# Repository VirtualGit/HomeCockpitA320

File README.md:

# A320 Home Cockpit
Home cockpit project of the Airbus A320 based on Arduino.

[Read more](https://github.com/VirtualGit/HomeCockpitA320/wiki/A320-Home-Cockpit)

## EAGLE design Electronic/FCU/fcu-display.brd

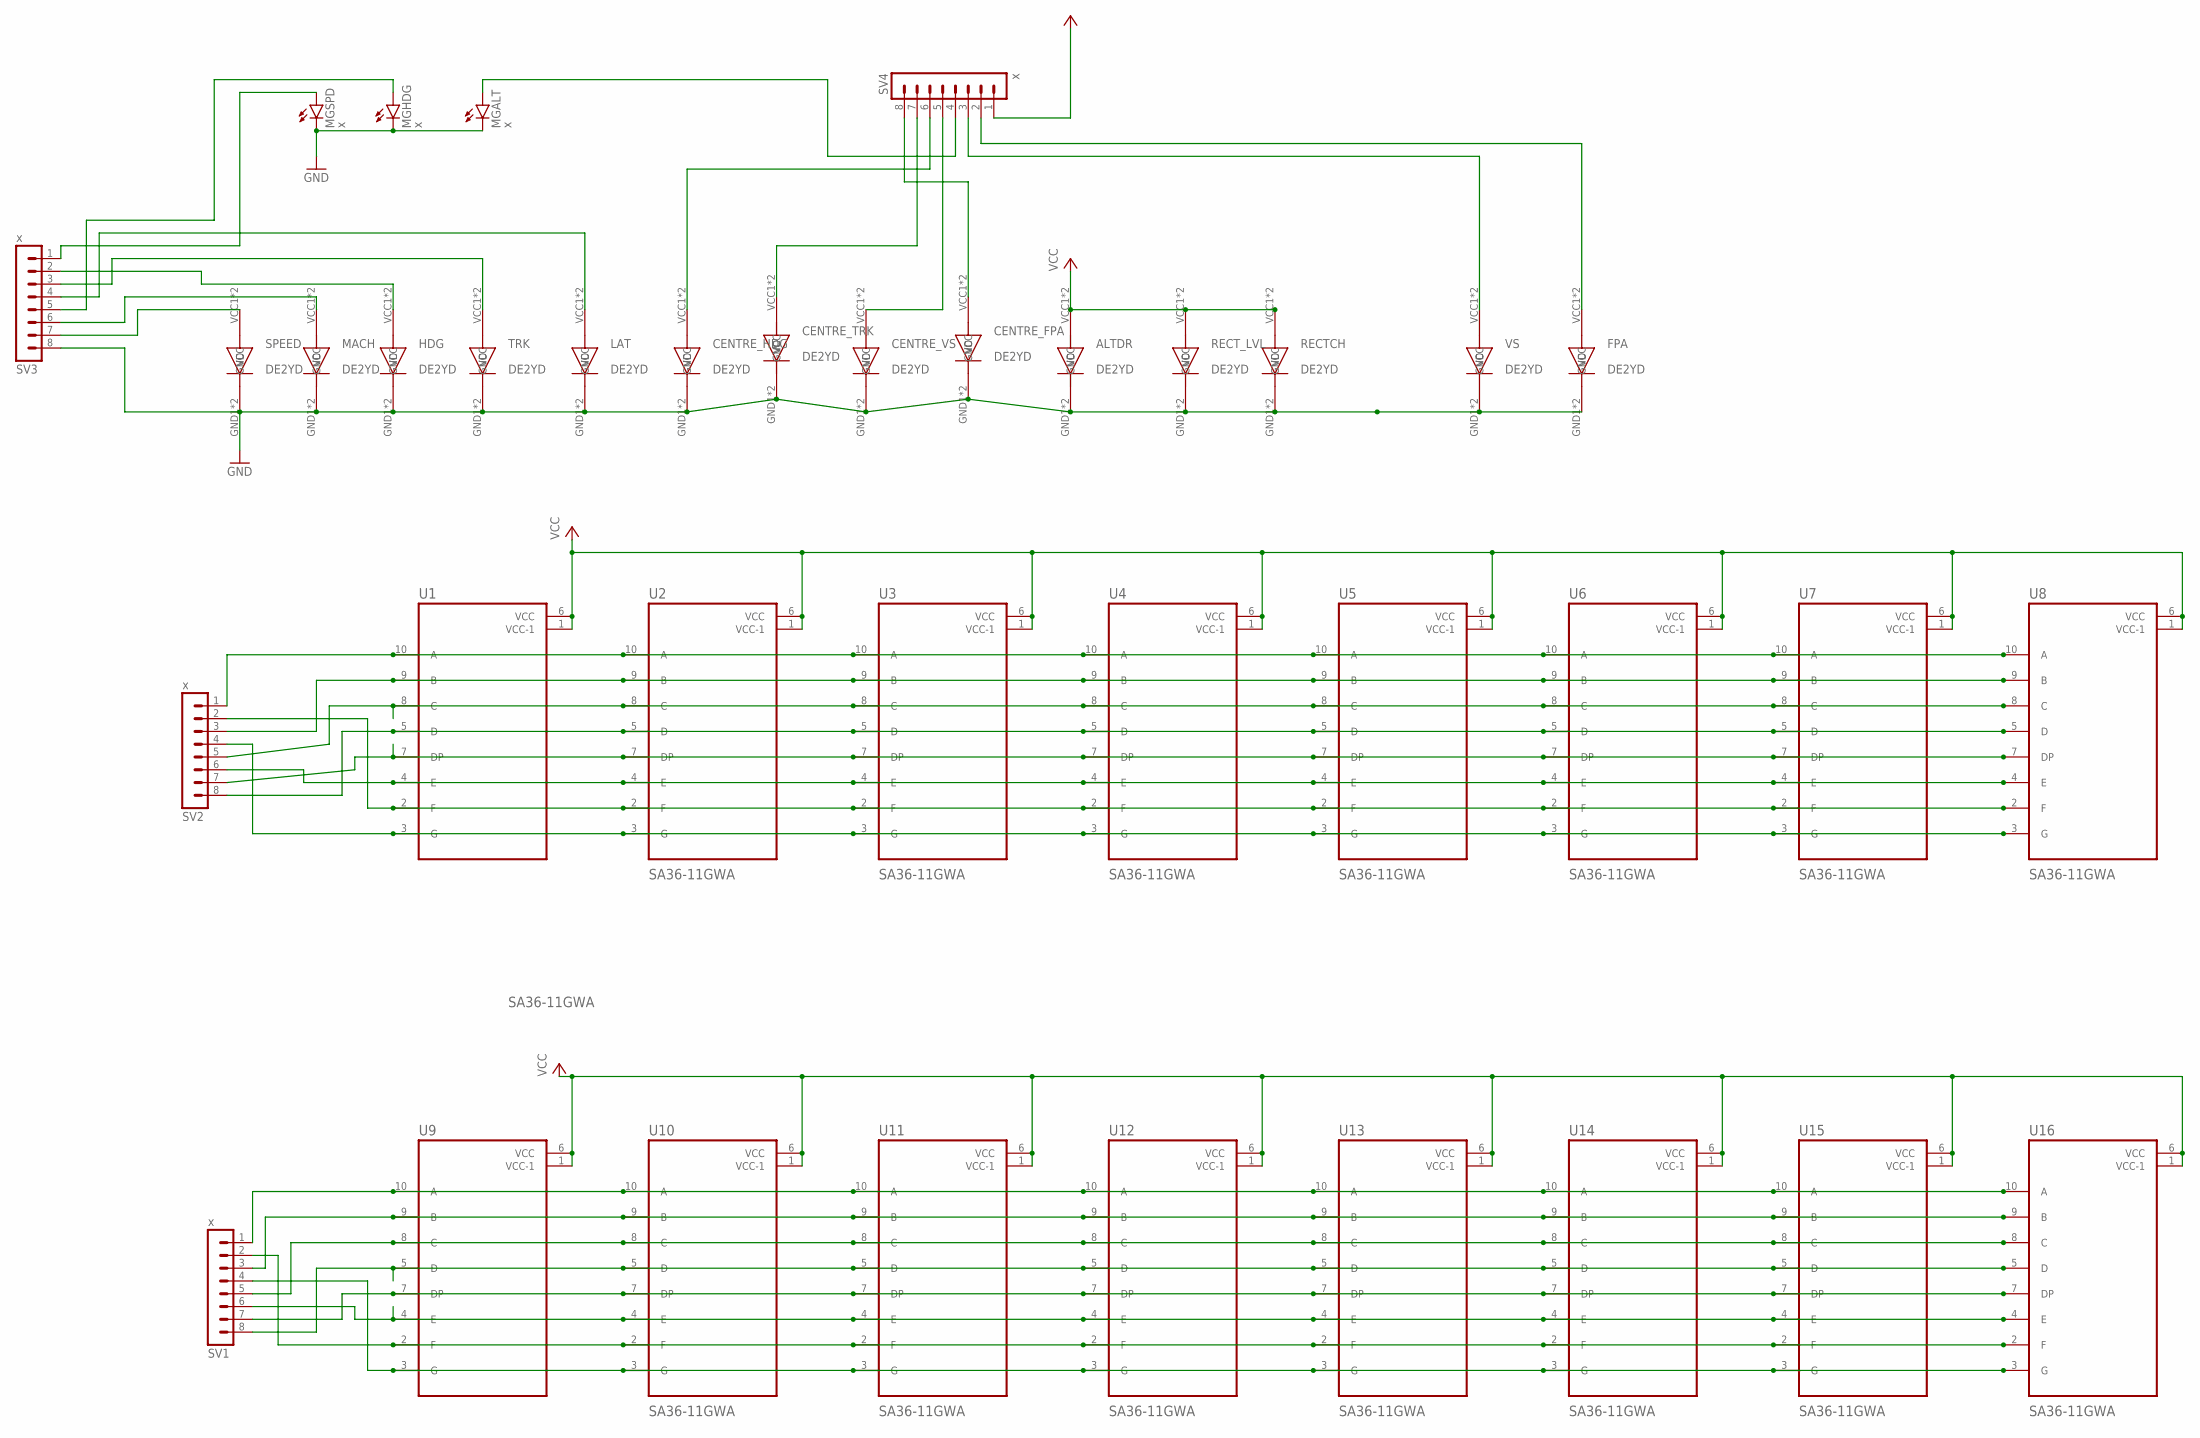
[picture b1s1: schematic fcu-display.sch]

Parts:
ALTDR: DE2YD; STANDARD
CENTRE_FPA: DE2YD; STANDARD
CENTRE_HDG: DE2YD; STANDARD
CENTRE_TRK: DE2YD; STANDARD
CENTRE_VS: DE2YD; STANDARD
FPA: DE2YD; STANDARD
HDG: DE2YD; STANDARD
LAT: DE2YD; STANDARD
MACH: DE2YD; STANDARD
MGALT: x; LED3MM
MGHDG: x; LED3MM
MGSPD: x; LED3MM
RECTCH: DE2YD; STANDARD
RECT_LVL: DE2YD; STANDARD
SPEED: DE2YD; STANDARD
SV1, SV2, SV3, SV4: x; MA08-1
TRK: DE2YD; STANDARD
U1, U2, U3, U4, U5, U6, U7, U8, U9, U10, U11, U12, U13, U14, U15, U16: SA36-11GWA; KINGBRIGHT_SC36-11SRWA
VS: DE2YD; STANDARD

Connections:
GND: ALTDR.GND1 (GND), ALTDR.GND2 (GND), CENTRE_FPA.GND1 (GND), CENTRE_FPA.GND2 (GND), CENTRE_HDG.GND1 (GND), CENTRE_HDG.GND2 (GND), CENTRE_TRK.GND1 (GND), CENTRE_TRK.GND2 (GND), CENTRE_VS.GND1 (GND), CENTRE_VS.GND2 (GND), FPA.GND1 (GND), FPA.GND2 (GND), HDG.GND1 (GND), HDG.GND2 (GND), LAT.GND1 (GND), LAT.GND2 (GND), MACH.GND1 (GND), MACH.GND2 (GND), MGALT.K (C), MGHDG.K (C), MGSPD.K (C), RECTCH.GND1 (GND), RECTCH.GND2 (GND), RECT_LVL.GND1 (GND), RECT_LVL.GND2 (GND), SPEED.GND1 (GND), SPEED.GND2 (GND), SV3.8, TRK.GND1 (GND), TRK.GND2 (GND), VS.GND1 (GND), VS.GND2 (GND)
unnamed: SV2.1, U1.10 (A), U2.10 (A), U3.10 (A), U4.10 (A), U5.10 (A), U6.10 (A), U7.10 (A), U8.10 (A)
unnamed: LAT.VCC1 (VCC), LAT.VCC2 (VCC), SV3.4
unnamed: SV2.5, U1.8 (C), U2.8 (C), U3.8 (C), U4.8 (C), U5.8 (C), U6.8 (C), U7.8 (C), U8.8 (C)
unnamed: MGSPD.A, SV3.1
unnamed: SV2.7, U1.7 (DP), U2.7 (DP), U3.7 (DP), U4.7 (DP), U5.7 (DP), U6.7 (DP), U7.7 (DP), U8.7 (DP)
unnamed: MGHDG.A, SV3.5
unnamed: SV2.2, U1.2 (F), U2.2 (F), U3.2 (F), U4.2 (F), U5.2 (F), U6.2 (F), U7.2 (F), U8.2 (F)
unnamed: FPA.VCC1 (VCC), FPA.VCC2 (VCC), SV4.2
unnamed: SV4.3, VS.VCC1 (VCC), VS.VCC2 (VCC)
unnamed: CENTRE_FPA.VCC1 (VCC), CENTRE_FPA.VCC2 (VCC), SV4.8
unnamed: CENTRE_TRK.VCC1 (VCC), CENTRE_TRK.VCC2 (VCC), SV4.7
unnamed: CENTRE_HDG.VCC1 (VCC), CENTRE_HDG.VCC2 (VCC), SV4.6
unnamed: SV1.1, U9.10 (A), U10.10 (A), U11.10 (A), U12.10 (A), U13.10 (A), U14.10 (A), U15.10 (A), U16.10 (A)
unnamed: SPEED.VCC1 (VCC), SPEED.VCC2 (VCC), SV3.7
unnamed: MACH.VCC1 (VCC), MACH.VCC2 (VCC), SV3.6
unnamed: SV1.5, U9.8 (C), U10.8 (C), U11.8 (C), U12.8 (C), U13.8 (C), U14.8 (C), U15.8 (C), U16.8 (C)
unnamed: HDG.VCC1 (VCC), HDG.VCC2 (VCC), SV3.2
unnamed: SV1.7, U9.7 (DP), U10.7 (DP), U11.7 (DP), U12.7 (DP), U13.7 (DP), U14.7 (DP), U15.7 (DP), U16.7 (DP)
unnamed: SV3.3, TRK.VCC1 (VCC), TRK.VCC2 (VCC)
unnamed: SV1.2, U9.2 (F), U10.2 (F), U11.2 (F), U12.2 (F), U13.2 (F), U14.2 (F), U15.2 (F), U16.2 (F)
unnamed: CENTRE_VS.VCC1 (VCC), CENTRE_VS.VCC2 (VCC), SV4.5
unnamed: MGALT.A, SV4.4
unnamed: SV1.4, U9.3 (G), U10.3 (G), U11.3 (G), U12.3 (G), U13.3 (G), U14.3 (G), U15.3 (G), U16.3 (G)
unnamed: SV1.6, U9.4 (E), U10.4 (E), U11.4 (E), U12.4 (E), U13.4 (E), U14.4 (E), U15.4 (E), U16.4 (E)
unnamed: SV1.8, U9.5 (D), U10.5 (D), U11.5 (D), U12.5 (D), U13.5 (D), U14.5 (D), U15.5 (D), U16.5 (D)
unnamed: SV1.3, U9.9 (B), U10.9 (B), U11.9 (B), U12.9 (B), U13.9 (B), U14.9 (B), U15.9 (B), U16.9 (B)
unnamed: SV2.4, U1.3 (G), U2.3 (G), U3.3 (G), U4.3 (G), U5.3 (G), U6.3 (G), U7.3 (G), U8.3 (G)
unnamed: SV2.6, U1.4 (E), U2.4 (E), U3.4 (E), U4.4 (E), U5.4 (E), U6.4 (E), U7.4 (E), U8.4 (E)
unnamed: SV2.8, U1.5 (D), U2.5 (D), U3.5 (D), U4.5 (D), U5.5 (D), U6.5 (D), U7.5 (D), U8.5 (D)
unnamed: SV2.3, U1.9 (B), U2.9 (B), U3.9 (B), U4.9 (B), U5.9 (B), U6.9 (B), U7.9 (B), U8.9 (B)
VCC: ALTDR.VCC1 (VCC), ALTDR.VCC2 (VCC), RECTCH.VCC1 (VCC), RECTCH.VCC2 (VCC), RECT_LVL.VCC1 (VCC), RECT_LVL.VCC2 (VCC), SV4.1, U1.1 (VCC-1), U1.6 (VCC), U2.1 (VCC-1), U2.6 (VCC), U3.1 (VCC-1), U3.6 (VCC), U4.1 (VCC-1), U4.6 (VCC), U5.1 (VCC-1), U5.6 (VCC), U6.1 (VCC-1), U6.6 (VCC), U7.1 (VCC-1), U7.6 (VCC), U8.1 (VCC-1), U8.6 (VCC), U9.1 (VCC-1), U9.6 (VCC), U10.1 (VCC-1), U10.6 (VCC), U11.1 (VCC-1), U11.6 (VCC), U12.1 (VCC-1), U12.6 (VCC), U13.1 (VCC-1), U13.6 (VCC), U14.1 (VCC-1), U14.6 (VCC), U15.1 (VCC-1), U15.6 (VCC), U16.1 (VCC-1), U16.6 (VCC)

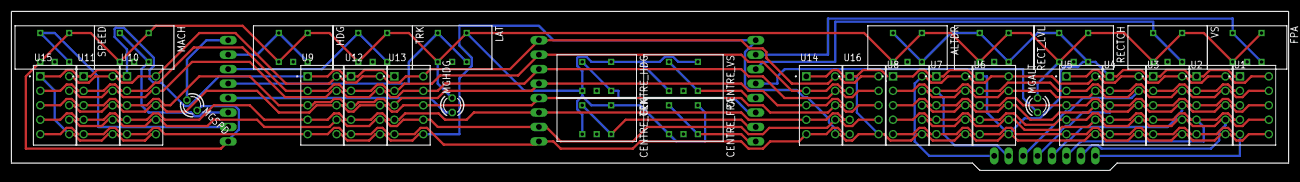
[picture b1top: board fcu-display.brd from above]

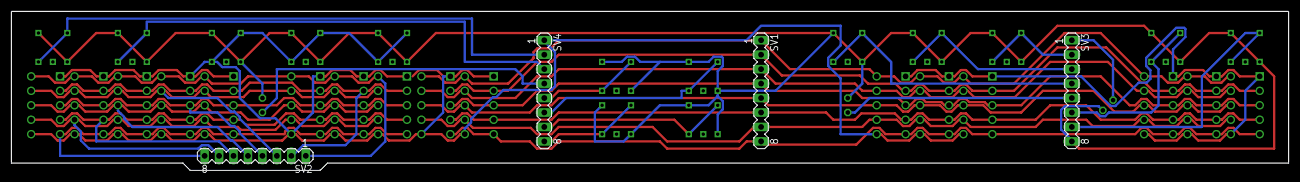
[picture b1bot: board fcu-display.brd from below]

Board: 2 copper layers, 224.5 x 27.9 mm, 37 parts (4 on the bottom side), 32 nets.

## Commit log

2020-01-19 Add Electronic folder and first EAGLE lib MAX7219
2020-02-03 Add Eagle libraries for FCU
2020-02-03 Add datasheets for FCU parts
2020-02-03 Add FCU schema and board, display part.
2021-02-13 First FCU draft with KiCad
2021-02-16 First draft complete for FCU MB (MotherBoard) and FCU Display.
2021-02-16 Remove old electronic files (Eagle)
2021-02-16 Add missing files
2021-02-16 Rename Electronic directory
2021-02-17 Add freerouting tool (from https://github.com/freerouting/freerouting)
2021-02-17 Remove draft schema
2021-02-17 Remove undesired, generated files
2021-02-17 Update gitignore file
2021-02-17 Update fcu schemas and libraries
2021-02-17 Update references to symbol in right library
2021-02-17 Update gitignore
2021-02-17 Remove undesired file
2021-02-17 Update FCU display board with routing
2021-02-17 Adust fcu display pcb layout Add Vcc to rotary encoder and update pcb with jst +1 pin
2021-02-20 Add first arduino libraries and test fcu file
2021-02-20 Add JHBridge software first draft version
2021-02-20 [JHBridge] Add tab for generating files
2021-02-21 Update JHBridge and JHArduino library to remove variable names
    Update JHBridge and JHArduino library to remove variable names and use
    an enum instead. All JeeHell parameters are in parameters.json. This
    file is the reference, from it, the parameters.h of JHArudino is
    generated. parameter.json is also used by JHBridge to generate JeeHell
    FMGSserver.iocp.ini file for a given board configuration (boards must be
    connected at the generation time to know which parameter are used and
2021-02-21 Add Analog_Buttons to the libraries
2021-02-21 Update SerialPort reading, because in case of quick new lines, readLine may stop in the middle of one line
2021-02-21 Update JHArduino library to send new values (buttons, then rotary encoders)
2021-02-21 Update fcu arduino test to add a button
2021-02-21 Add rotary encoder library
2021-02-21 Update parameter.json to add a rotary parameter
2021-02-21 Add a rotary encoder to the fcu test arduino project
2021-02-21 Add Arduino micro symbol and footprint
2021-02-21 Normalize parameters.json
2021-02-23 Update FCU PCB net routing
2021-02-25 Finalise first FCU PCB version
2021-02-25 Ignore gerber files
2021-04-02 switch types from int to long
2021-04-02 Update parameters.h file of JHArduino lib
2021-04-02 Update LedControl lib for improving common anode behavior.
2021-04-02 Update fcu arduino soft : digits and rotary encoders are ok
2021-04-07 Add information on identification log
2021-04-07 Change variable size type to size_t
2021-04-07 Change JHBridge default tab
2021-04-07 Update parameters.json file with new consolidated informations
2021-04-07 Change the way JHBridge handle SIOCVariable to allow correct export to both Arduino library and FMGS config file
2021-04-11 Update electornic schema of FCU MotherBoard and Display. Replace MAX7219 for leds to dedicated TLC5917.
2021-04-11 Adjust resistor values for TLC5917
2021-04-11 PCB changed after gerber export
2021-04-11 Add FCU PCB images
